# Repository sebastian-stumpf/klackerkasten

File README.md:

# Klackerkasten

Note: If you are not hand solerding the components then triple check the component orientation. I went
the PCBA route with JLC and there were two rotated components.

# Acknowledgments

- Weteor for his amazing BrkOut which was a big inspiration.
- NcKiser for the STM32F072\_template which helped me a lot for this project.
- The mad crowd of the Clack Tales discord server. Thanks for answering all my endless questions!

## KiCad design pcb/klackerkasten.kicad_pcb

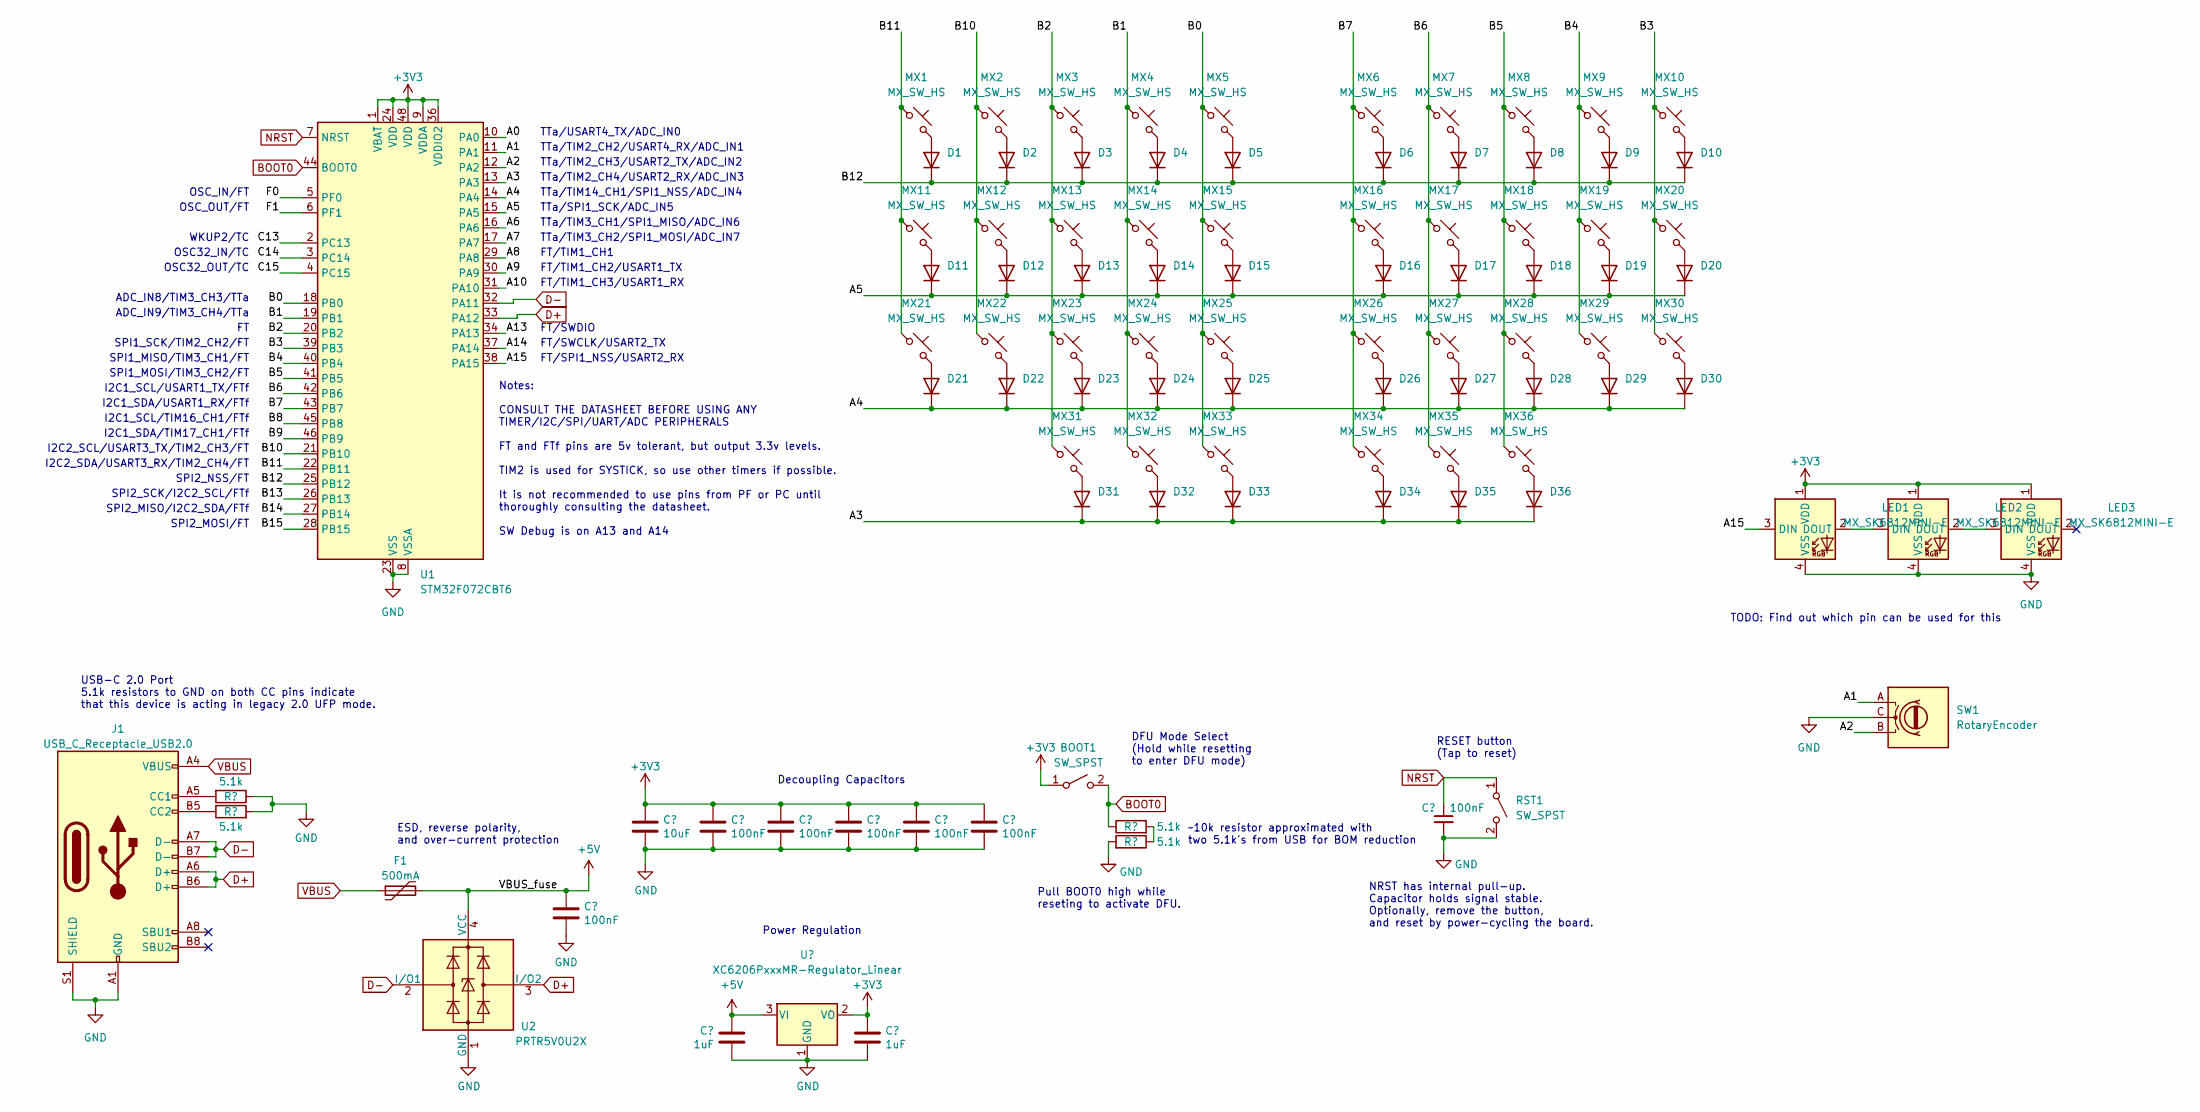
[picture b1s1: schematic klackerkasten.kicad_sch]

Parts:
BOOT1: SW_SPST; SW_SPST_TL3342; LCSC C318884
C1, C3, C4, C5, C6, C7, C8: 100nF; C_0402_1005Metric; LCSC C307331
C2: 10uF; C_0603_1608Metric; LCSC C307331
C9, C10: 1uF; C_0402_1005Metric; LCSC C307331
D1, D2, D3, D4, D5, D6, D7, D8, D9, D10, D11, D12, D13, D14, D15, D16, D17, D18, D19, D20, D21, D22, D23, D24, D25, D26, D27, D28, D29, D30, D31, D32, D33, D34, D35, D36: 1N4148W; D_SOD-123; LCSC C81598
F1: 500mA; Fuse_1206_3216Metric; LCSC C135341
J1: USB_C_Receptacle_USB2.0; USB_C_Receptacle_HRO_TYPE-C-31-M-12; JlcRotOffset 180
LED1, LED2, LED3: MX_SK6812MINI-E; LED_6028R; LCSC C5149201
MX1, MX2, MX3, MX4, MX5, MX6, MX7, MX8, MX9, MX10, MX11, MX12, MX13, MX14, MX15, MX16, MX17, MX18, MX19, MX20, MX21, MX22, MX23, MX24, MX25, MX26, MX27, MX28, MX29, MX30, MX31, MX32, MX35, MX36: MX_SW_HS; SW_MX_HS_CPG151101S11_1u; LCSC C5156480
MX33, MX34: MX_SW_HS; SW_MX_HS_CPG151101S11_1.5u; LCSC C5156480
R1, R2, R3, R4: 5.1k; R_0402_1005Metric; LCSC C25905
RST1: SW_SPST; SW_SPST_TL3342; LCSC C318884
SW1: RotaryEncoder; RotaryEncoder_Alps_EC12E_Vertical_H20mm
U1: STM32F072CBT6; LQFP-48_7x7mm_P0.5mm; JlcRotOffset 90
U2: PRTR5V0U2X; SOT-143; LCSC C2827688
U3: XC6206PxxxMR-Regulator_Linear; SOT-23; LCSC C5446

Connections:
+3V3: BOOT1.1 (A), C2.1, C3.1, C4.1, C5.1, C6.1, C7.1, C10.1, LED1.1 (VDD), LED2.1 (VDD), LED3.1 (VDD), U1.1 (VBAT), U1.9 (VDDA), U1.24 (VDD), U1.36 (VDDIO2), U1.48 (VDD), U3.2 (VO)
+5V: C8.1, C9.1, F1.2, U2.4 (VCC), U3.3 (VI)
/A0: U1.10 (PA0)
/A1: SW1.A, U1.11 (PA1)
/A2: SW1.B, U1.12 (PA2)
/A3: D31.1 (K), D32.1 (K), D33.1 (K), D34.1 (K), D35.1 (K), D36.1 (K), U1.13 (PA3)
/A4: D21.1 (K), D22.1 (K), D23.1 (K), D24.1 (K), D25.1 (K), D26.1 (K), D27.1 (K), D28.1 (K), D29.1 (K), D30.1 (K), U1.14 (PA4)
/A5: D11.1 (K), D12.1 (K), D13.1 (K), D14.1 (K), D15.1 (K), D16.1 (K), D17.1 (K), D18.1 (K), D19.1 (K), D20.1 (K), U1.15 (PA5)
/A6: U1.16 (PA6)
/A7: U1.17 (PA7)
/A8: U1.29 (PA8)
/A9: U1.30 (PA9)
/A10: U1.31 (PA10)
/A13: U1.34 (PA13)
/A14: U1.37 (PA14)
/A15: LED1.3 (DIN), U1.38 (PA15)
/B0: MX5.1, MX15.1, MX25.1, MX33.1, U1.18 (PB0)
/B1: MX4.1, MX14.1, MX24.1, MX32.1, U1.19 (PB1)
/B2: MX3.1, MX13.1, MX23.1, MX31.1, U1.20 (PB2)
/B3: MX10.1, MX20.1, MX30.1, U1.39 (PB3)
/B4: MX9.1, MX19.1, MX29.1, U1.40 (PB4)
/B5: MX8.1, MX18.1, MX28.1, MX36.1, U1.41 (PB5)
/B6: MX7.1, MX17.1, MX27.1, MX35.1, U1.42 (PB6)
/B7: MX6.1, MX16.1, MX26.1, MX34.1, U1.43 (PB7)
/B8: U1.45 (PB8)
/B9: U1.46 (PB9)
/B10: MX2.1, MX12.1, MX22.1, U1.21 (PB10)
/B11: MX1.1, MX11.1, MX21.1, U1.22 (PB11)
/B12: D1.1 (K), D2.1 (K), D3.1 (K), D4.1 (K), D5.1 (K), D6.1 (K), D7.1 (K), D8.1 (K), D9.1 (K), D10.1 (K), U1.25 (PB12)
/B13: U1.26 (PB13)
/B14: U1.27 (PB14)
/B15: U1.28 (PB15)
/C13: U1.2 (PC13)
/C14: U1.3 (PC14)
/C15: U1.4 (PC15)
/F0: U1.5 (PF0)
/F1: U1.6 (PF1)
BOOT0: BOOT1.2 (B), R3.1, U1.44 (BOOT0)
D+: J1.A6 (D+), J1.B6 (D+), U1.33 (PA12), U2.3 (I/O2)
D-: J1.A7 (D-), J1.B7 (D-), U1.32 (PA11), U2.2 (I/O1)
GND: C1.2, C2.2, C3.2, C4.2, C5.2, C6.2, C7.2, C8.2, C9.2, C10.2, J1.A1 (GND), J1.A12 (GND), J1.B1 (GND), J1.B12 (GND), J1.S1 (SHIELD), LED1.4 (VSS), LED2.4 (VSS), LED3.4 (VSS), R1.1, R2.2, R4.2, RST1.2 (B), SW1.C, U1.8 (VSSA), U1.23 (VSS), U1.35 (VSS), U1.47 (VSS), U2.1 (GND), U3.1 (GND)
NRST: C1.1, RST1.1 (A), U1.7 (NRST)
unnamed: D1.2 (A), MX1.2
unnamed: D2.2 (A), MX2.2
unnamed: D3.2 (A), MX3.2
unnamed: D4.2 (A), MX4.2
unnamed: D5.2 (A), MX5.2
unnamed: D6.2 (A), MX6.2
unnamed: D7.2 (A), MX7.2
unnamed: D8.2 (A), MX8.2
unnamed: D9.2 (A), MX9.2
unnamed: D10.2 (A), MX10.2
unnamed: D11.2 (A), MX11.2
unnamed: D12.2 (A), MX12.2
unnamed: D13.2 (A), MX13.2
unnamed: D14.2 (A), MX14.2
unnamed: D15.2 (A), MX15.2
unnamed: D16.2 (A), MX16.2
unnamed: D17.2 (A), MX17.2
unnamed: D18.2 (A), MX18.2
unnamed: D19.2 (A), MX19.2
unnamed: D20.2 (A), MX20.2
unnamed: D21.2 (A), MX21.2
unnamed: D22.2 (A), MX22.2
unnamed: D23.2 (A), MX23.2
unnamed: D24.2 (A), MX24.2
unnamed: D25.2 (A), MX25.2
unnamed: D26.2 (A), MX26.2
unnamed: D27.2 (A), MX27.2
unnamed: D28.2 (A), MX28.2
unnamed: D29.2 (A), MX29.2
unnamed: D30.2 (A), MX30.2
unnamed: D31.2 (A), MX31.2
unnamed: D32.2 (A), MX32.2
unnamed: D33.2 (A), MX33.2
unnamed: D34.2 (A), MX34.2
unnamed: D35.2 (A), MX35.2
unnamed: D36.2 (A), MX36.2
unnamed: J1.A5 (CC1), R1.2
unnamed: J1.B5 (CC2), R2.1
unnamed: LED1.2 (DOUT), LED2.3 (DIN)
unnamed: LED2.2 (DOUT), LED3.3 (DIN)
unnamed: R3.2, R4.1
VBUS: F1.1, J1.A4 (VBUS), J1.A9 (VBUS), J1.B4 (VBUS), J1.B9 (VBUS)

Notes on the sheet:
SPI1_SCK/TIM2_CH2/FT
FT/TIM1_CH1
FT/TIM1_CH3/USART1_RX
SPI2_NSS/FT
Notes: CONSULT THE DATASHEET BEFORE USING ANY TIMER/I2C/SPI/UART/ADC PERIPHERALS FT and FTf pins are 5v tolerant, but output 3.3v levels. TIM2 is used for SYSTICK, so use other timers if possible. It is not recommended to use pins from PF or PC until thoroughly consulting the datasheet. SW Debug is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
TTa/TIM2_CH4/USART2_RX/ADC_IN3
NRST has internal pull-up. Capacitor holds signal stable. Optionally, remove the button, and reset by power-cycling the board.
FT/SWDIO
Decoupling Capacitors
SPI1_MOSI/TIM3_CH2/FT
ADC_IN9/TIM3_CH4/TTa
I2C2_SCL/USART3_TX/TIM2_CH3/FT
SPI2_MISO/I2C2_SDA/FTf
FT/SWCLK/USART2_TX
I2C1_SCL/TIM16_CH1/FTf
~10k resistor approximated with two 5.1k's from USB for BOM reduction
TTa/TIM2_CH2/USART4_RX/ADC_IN1
USB-C 2.0 Port 5.1k resistors to GND on both CC pins indicate that this device is acting in legacy 2.0 UFP mode.
TTa/TIM2_CH3/USART2_TX/ADC_IN2
OSC_IN/FT
DFU Mode Select (Hold while resetting to enter DFU mode)
WKUP2/TC
I2C2_SDA/USART3_RX/TIM2_CH4/FT
ADC_IN8/TIM3_CH3/TTa
RESET button (Tap to reset)
Pull BOOT0 high while reseting to activate DFU.
I2C1_SDA/TIM17_CH1/FTf
TTa/SPI1_SCK/ADC_IN5
TTa/TIM3_CH1/SPI1_MISO/ADC_IN6
TTa/TIM3_CH2/SPI1_MOSI/ADC_IN7
OSC32_OUT/TC
FT/SPI1_NSS/USART2_RX
SPI1_MISO/TIM3_CH1/FT
OSC32_IN/TC
TODO: Find out which pin can be used for this
TTa/TIM14_CH1/SPI1_NSS/ADC_IN4
I2C1_SDA/USART1_RX/FTf
SPI2_MOSI/FT
FT/TIM1_CH2/USART1_TX
Power Regulation

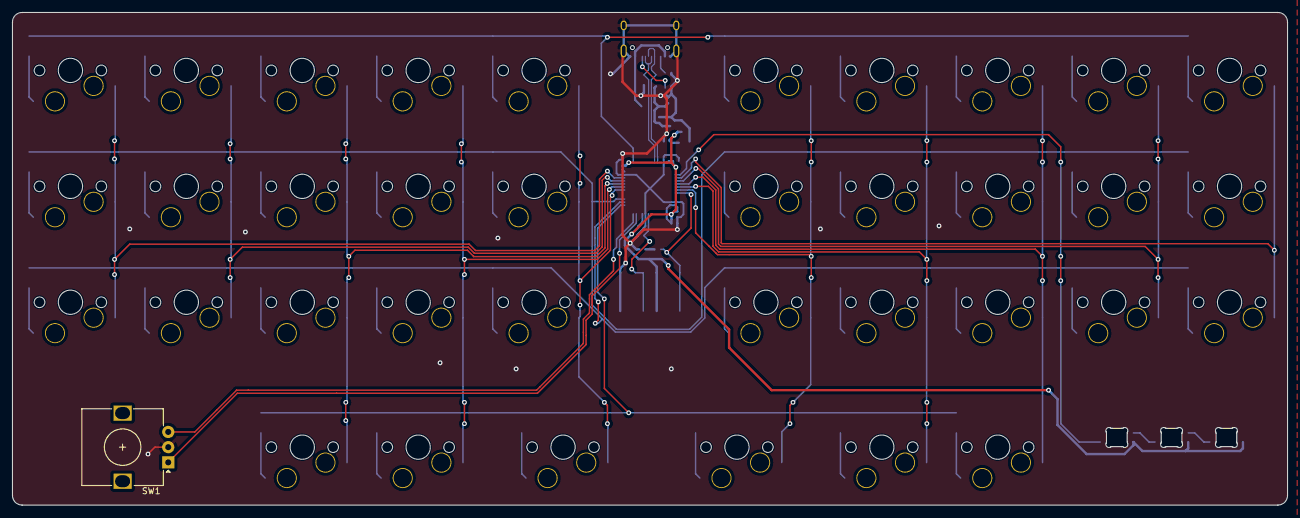
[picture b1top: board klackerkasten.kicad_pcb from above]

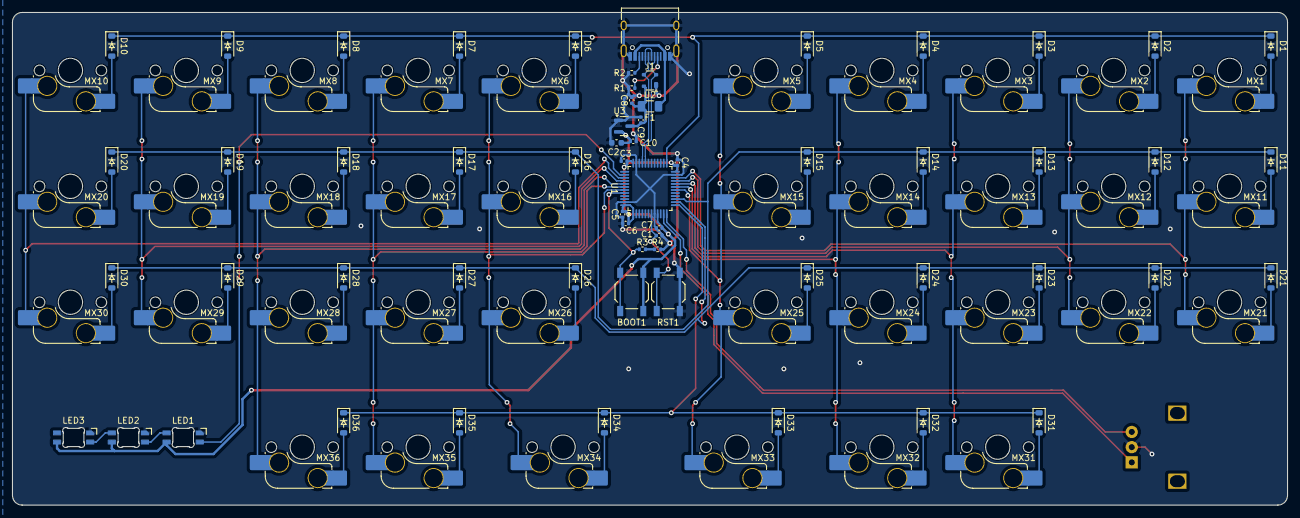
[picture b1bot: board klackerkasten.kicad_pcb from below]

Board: 2 copper layers, 209.5 x 81.0 mm, 97 parts (96 on the bottom side), 66 nets.

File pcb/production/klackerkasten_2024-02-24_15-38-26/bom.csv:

Designator,Footprint,Quantity,Value,LCSC Part #
"BOOT1, RST1",SW_SPST_TL3342,2,SW_SPST,C318884
"C1, C3, C4, C5, C6, C7, C8",402,7,100nF,C307331
"C10, C9",402,2,1uF,C52923
C2,603,1,10uF,C19702
"D1, D10, D11, D12, D13, D14, D15, D16, D17, D18, D19, D2, D20, D21, D22, D23, D24, D25, D26, D27, D28, D29, D3, D30, D31, D32, D33, D34, D35, D36, D4, D5, D6, D7, D8, D9",D_SOD-123,36,1N4148W,C81598
F1,1206,1,500mA,C369160
J1,USB_C_Receptacle_HRO_TYPE-C-31-M-12,1,USB_C_Receptacle_USB2.0,C165948
"R1, R2, R3, R4",402,4,5.1k,C25905
U1,LQFP-48_7x7mm_P0.5mm,1,STM32F072CBT6,C81720
U2,SOT-143,1,PRTR5V0U2X,C2827688
U3,SOT-23,1,XC6206PxxxMR-Regulator_Linear,C5446
